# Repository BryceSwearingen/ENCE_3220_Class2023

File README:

This is the readme for embedded systems, more info to be added.

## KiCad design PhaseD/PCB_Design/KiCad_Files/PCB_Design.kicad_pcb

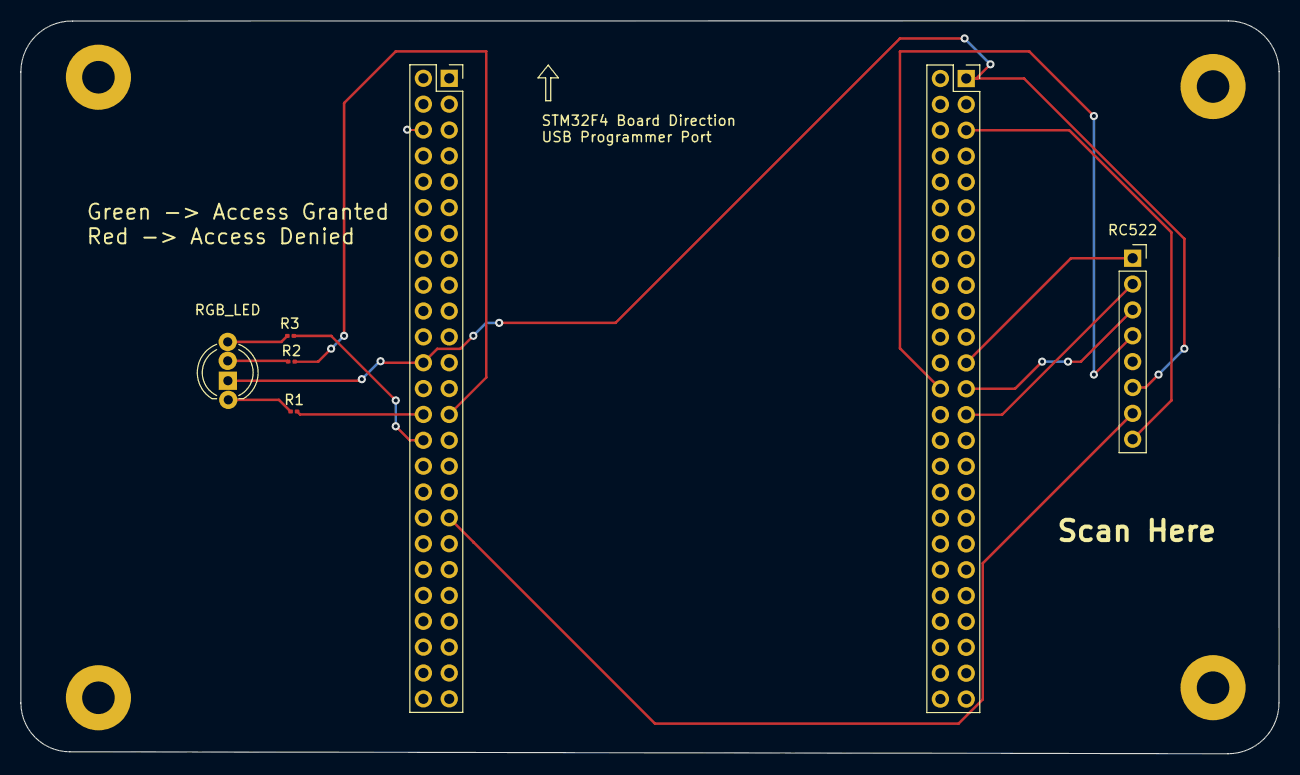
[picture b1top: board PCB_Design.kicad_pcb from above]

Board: 2 copper layers, 123.6 x 72.0 mm, 11 parts (0 on the bottom side), 13 nets.

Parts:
H1, H2, H3, H4: MountingHole; MountingHole_3.2mm_M3_Pad
J1: Discovery Board Conn 1; PinSocket_2x25_P2.54mm_Vertical
J2: Discovery Board Conn 2; PinSocket_2x25_P2.54mm_Vertical
R1, R2, R3: 330; R_0201_0603Metric
RC522: RFID-RC522-MODULE; PinSocket_1x08_P2.54mm_Vertical
RGB_LED: LED_ABGR; LED_D5.0mm-4_RGB_Wide_Pins

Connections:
+3V0: J2.5, RC522.8 (3.3V)
Blue: J1.30, R3.1
GND: J1.24, J2.1, RC522.6 (GND), RGB_LED.1 (A)
Green: J1.27, R2.1
MISO: J2.26, RC522.4 (MISO)
MOSI: J2.25, RC522.3 (MOSI)
unnamed: R3.2, RGB_LED.2 (BK)
unnamed: R2.2, RGB_LED.3 (GK)
unnamed: R1.2, RGB_LED.4 (RK)
RST: J1.35, RC522.7 (RST)
Red: J1.28, R1.1
SCK: J2.27, RC522.2 (SCK)
SDA: J2.23, RC522.1 (SDA)

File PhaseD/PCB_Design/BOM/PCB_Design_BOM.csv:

"Id";"Designator";"Footprint";"Quantity";"Designation";"Supplier and ref";
1;"J2";"PinSocket_2x25_P2.54mm_Vertical";1;"Discovery Board Conn 2";;;
2;"H3,H4,H1,H2";"MountingHole_3.2mm_M3_Pad";4;"MountingHole";;;
3;"R2,R1,R3";"R_0201_0603Metric";3;"330";;;
4;"J1";"PinSocket_2x25_P2.54mm_Vertical";1;"Discovery Board Conn 1";;;
5;"RGB_LED";"LED_D5.0mm-4_RGB_Wide_Pins";1;"LED_ABGR";;;
6;"RC522";"PinSocket_1x08_P2.54mm_Vertical";1;"RFID-RC522-MODULE";;;

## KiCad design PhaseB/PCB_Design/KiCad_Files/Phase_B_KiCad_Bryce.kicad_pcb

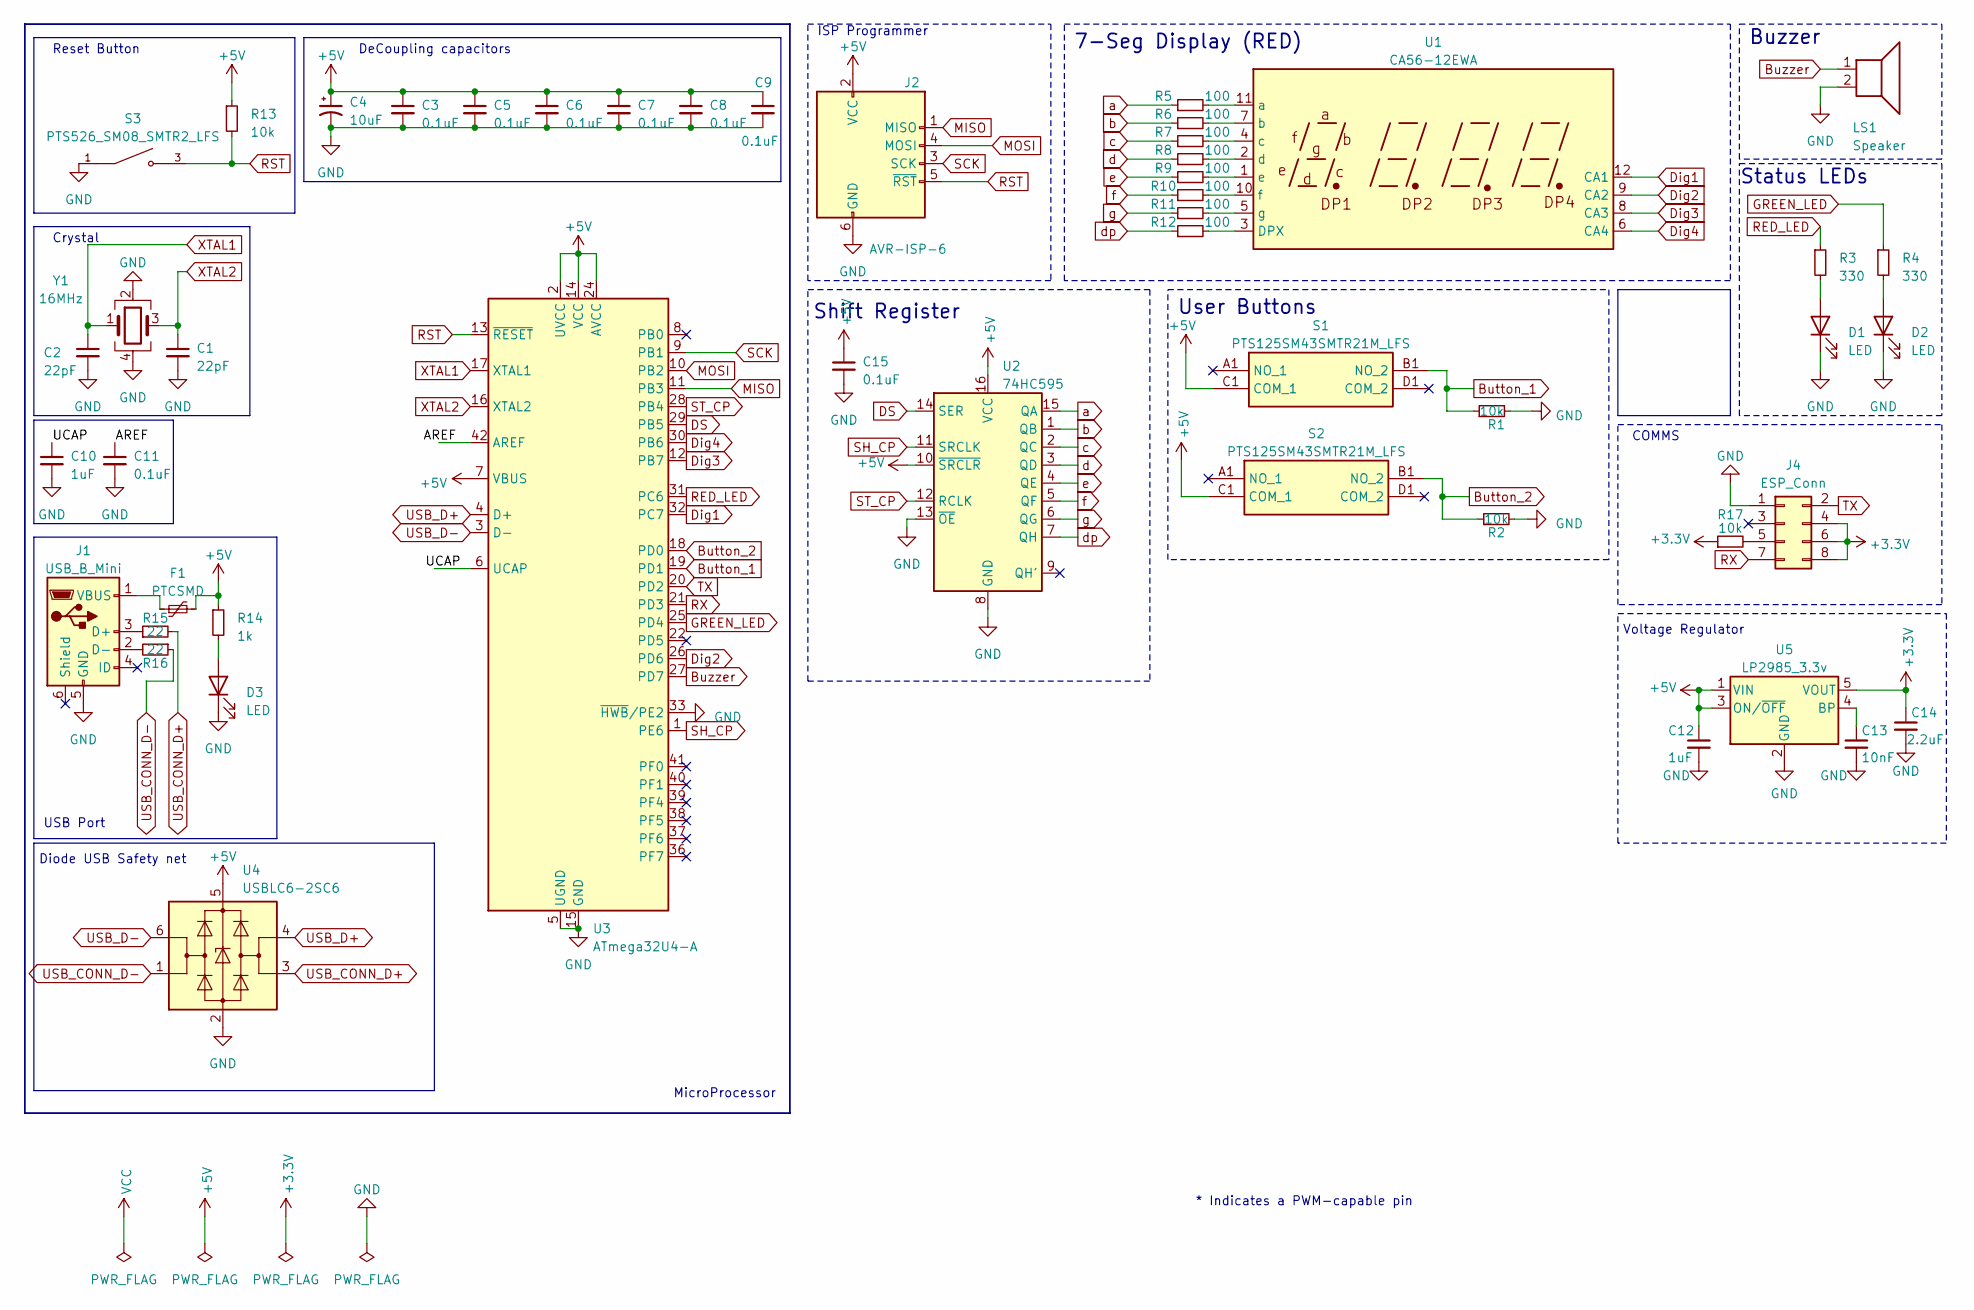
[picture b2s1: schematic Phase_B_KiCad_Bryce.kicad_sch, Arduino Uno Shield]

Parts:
C1, C2: 22pF; C_0603_1608Metric
C3, C5, C6, C7, C8, C9, C11, C15: 0.1uF; C_0603_1608Metric
C4: 10uF; C_0805_2012Metric
C10, C12: 1uF; C_0603_1608Metric
C13: 10nF; C_0603_1608Metric
C14: 2.2uF; C_0603_1608Metric
D1, D2, D3: LED; LED_0805_2012Metric
F1: PTCSMD; Fuse_1812_4532Metric
J1: USB_B_Mini; USB_Mini-B_Lumberg_2486_01_Horizontal
J2: AVR-ISP-6; PinSocket_2x03_P2.54mm_Vertical
J4: ESP_Conn; PinSocket_2x04_P2.54mm_Vertical
LS1: Speaker; Buzzer_12x9.5RM7.6
R1, R2, R13, R17: 10k; R_0603_1608Metric
R3, R4: 330; R_0805_2012Metric
R5, R6, R7, R8, R9, R10, R11, R12: 100; R_0805_2012Metric
R14: 1k; R_0603_1608Metric
R15, R16: 22; R_0603_1608Metric
S1, S2: PTS125SM43SMTR21M_LFS; PTS125_SMD_Button; Manufacturer_Part_Number PTS125SM43SMTR21M LFS; Mouser Part Number 611-PTS125S43SMTRLFS
S3: PTS526_SM08_SMTR2_LFS; PTS526_SMD_Button; PARTREV 20 mar 19
U1: CA56-12EWA
U2: 74HC595; TSSOP-16_4.4x5mm_P0.65mm
U3: ATmega32U4-A; TQFP-44_10x10mm_P0.8mm
U4: USBLC6-2SC6; SOT-23-6
U5: LP2985_3.3v; SOT-23-5
Y1: 16MHz; Crystal_SMD_Abracon_ABM8G-4Pin_3.2x2.5mm

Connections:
+3V3: C14.1, J4.4, J4.6, J4.8, R17.1, U5.5 (VOUT)
+5V: C3.1, C4.1, C5.1, C6.1, C7.1, C8.1, C9.1, C12.1, C15.1, F1.2, J2.2 (VCC), R13.1, R14.1, S1.C1 (COM_1), S2.C1 (COM_1), U2.10 (~SRCLR), U2.16 (VCC), U3.2 (UVCC), U3.7 (VBUS), U3.14 (VCC), U3.24 (AVCC), U3.34 (VCC), U3.44 (AVCC), U4.5 (VBUS), U5.1 (VIN), U5.3 (ON/~OFF)
/AREF: C11.1, U3.42 (AREF)
/UCAP: C10.1, U3.6 (UCAP)
Button_1: R1.1, S1.B1 (NO_2), U3.19 (PD1)
Button_2: R2.1, S2.B1 (NO_2), U3.18 (PD0)
Buzzer: LS1.1, U3.27 (PD7)
DS: U2.14 (SER), U3.29 (PB5)
Dig1: U1.12 (CA1), U3.32 (PC7)
Dig2: U1.9 (CA2), U3.26 (PD6)
Dig3: U1.8 (CA3), U3.12 (PB7)
Dig4: U1.6 (CA4), U3.30 (PB6)
GND: C1.2, C2.2, C3.2, C4.2, C5.2, C6.2, C7.2, C8.2, C9.2, C10.2, C11.2, C12.2, C13.2, C14.2, C15.2, D1.1 (K), D2.1 (K), D3.1 (K), J1.5 (GND), J2.6 (GND), J4.1, LS1.2, R1.2, R2.2, S3.1, U2.8 (GND), U2.13 (~OE), U3.5 (UGND), U3.15 (GND), U3.23 (GND), U3.33 (~HWB/PE2), U3.35 (GND), U3.43 (GND), U4.2 (GND), U5.2 (GND), Y1.2, Y1.4
GREEN_LED: R4.1, U3.25 (PD4)
MISO: J2.1 (MISO), U3.11 (PB3)
MOSI: J2.4 (MOSI), U3.10 (PB2)
unnamed: D1.2 (A), R3.2
unnamed: D2.2 (A), R4.2
unnamed: D3.2 (A), R14.2
unnamed: J1.3 (D+), R15.1
unnamed: J1.2 (D-), R16.2
unnamed: F1.1, J1.1 (VBUS)
unnamed: J4.5, R17.2
unnamed: R12.2, U1.3 (DPX)
unnamed: R5.2, U1.11 (a)
unnamed: R6.2, U1.7 (b)
unnamed: R7.2, U1.4 (c)
unnamed: R8.2, U1.2 (d)
unnamed: R9.2, U1.1 (e)
unnamed: R10.2, U1.10 (f)
unnamed: R11.2, U1.5 (g)
unnamed: C13.1, U5.4 (BP)
RED_LED: R3.1, U3.31 (PC6)
RST: J2.5 (~RST), R13.2, S3.3, U3.13 (~RESET)
RX: J4.7, U3.21 (PD3)
SCK: J2.3 (SCK), U3.9 (PB1)
SH_CP: U2.11 (SRCLK), U3.1 (PE6)
ST_CP: U2.12 (RCLK), U3.28 (PB4)
TX: J4.2, U3.20 (PD2)
USB_CONN_D+: R15.2, U4.3 (I/O2)
USB_CONN_D-: R16.1, U4.1 (I/O1)
USB_D+: U3.4 (D+), U4.4 (I/O2)
USB_D-: U3.3 (D-), U4.6 (I/O1)
XTAL1: C2.1, U3.17 (XTAL1), Y1.1
XTAL2: C1.1, U3.16 (XTAL2), Y1.3
a: R5.1, U2.15 (QA)
b: R6.1, U2.1 (QB)
c: R7.1, U2.2 (QC)
d: R8.1, U2.3 (QD)
dp: R12.1, U2.7 (QH)
e: R9.1, U2.4 (QE)
f: R10.1, U2.5 (QF)
g: R11.1, U2.6 (QG)

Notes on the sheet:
Shift Register
USB Port
Voltage Regulator
Status LEDs
MicroProcessor
DeCoupling capacitors
User Buttons
Buzzer
ISP Programmer
Reset Button
* Indicates a PWM-capable pin
COMMS
Crystal
7-Seg Display (RED)
Diode USB Safety net

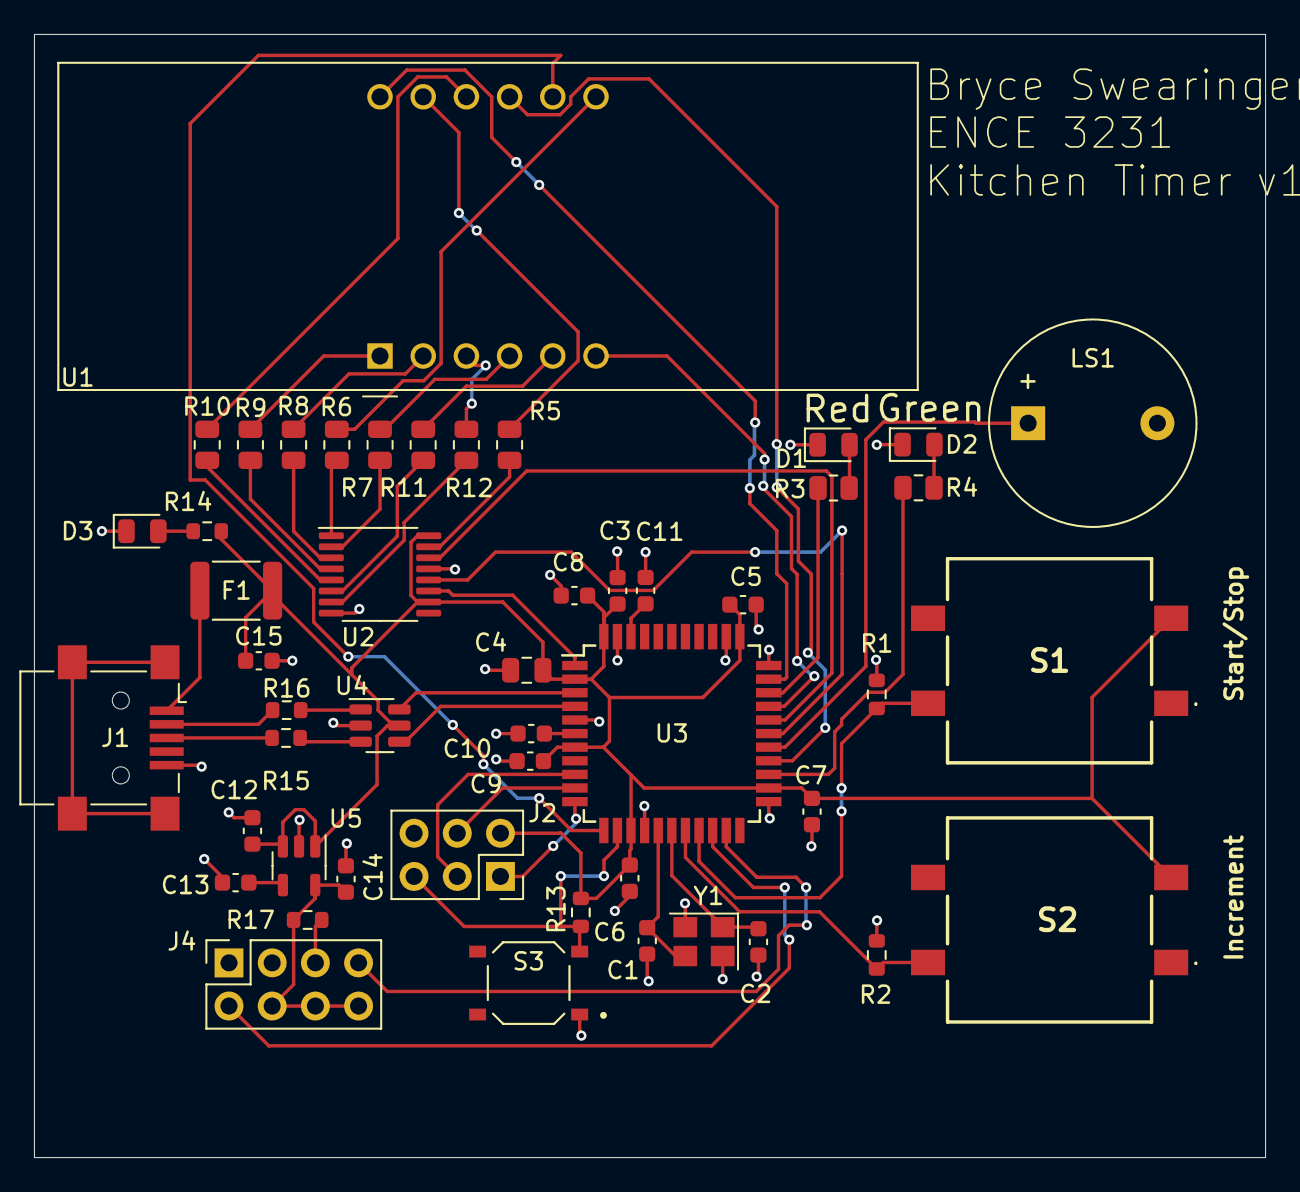
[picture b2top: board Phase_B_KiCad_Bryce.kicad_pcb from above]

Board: 2 copper layers, 72.4 x 66.0 mm, 49 parts (0 on the bottom side), 53 nets.

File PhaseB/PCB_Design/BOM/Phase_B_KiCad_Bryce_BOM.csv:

"Id";"Designator";"Footprint";"Quantity";"Designation";"Supplier and ref";
1;"R12,R9,R5,R7,R10,R8,R6,R11";"R_0805_2012Metric";8;"100";;;
2;"S3";"PTS526_SMD_Button";1;"PTS526_SM08_SMTR2_LFS";;;
3;"R14";"R_0603_1608Metric";1;"1k";;;
4;"U2";"TSSOP-16_4.4x5mm_P0.65mm";1;"74HC595";;;
5;"LS1";"Buzzer_12x9.5RM7.6";1;"Speaker";;;
6;"C12,C10";"C_0603_1608Metric";2;"1uF";;;
7;"C8,C3,C15,C9,C11,C5,C7,C6";"C_0603_1608Metric";8;"0.1uF";;;
8;"J4";"PinSocket_2x04_P2.54mm_Vertical";1;"ESP_Conn";;;
9;"F1";"Fuse_1812_4532Metric";1;"PTCSMD";;;
10;"D3,D1,D2";"LED_0805_2012Metric";3;"LED";;;
11;"U4";"SOT-23-6";1;"USBLC6-2SC6";;;
12;"R17,R1,R2,R13";"R_0603_1608Metric";4;"10k";;;
13;"Y1";"Crystal_SMD_Abracon_ABM8G-4Pin_3.2x2.5mm";1;"16MHz";;;
14;"C4";"C_0805_2012Metric";1;"10uF";;;
15;"J2";"PinSocket_2x03_P2.54mm_Vertical";1;"AVR-ISP-6";;;
16;"C14";"C_0603_1608Metric";1;"2.2uF";;;
17;"R3,R4";"R_0805_2012Metric";2;"330";;;
18;"R16,R15";"R_0603_1608Metric";2;"22";;;
19;"J1";"USB_Mini-B_Lumberg_2486_01_Horizontal";1;"USB_B_Mini";;;
20;"U5";"SOT-23-5";1;"LP2985_3.3v";;;
21;"S2,S1";"PTS125_SMD_Button";2;"PTS125SM43SMTR21M_LFS";;;
22;"C13";"C_0603_1608Metric";1;"10nF";;;
23;"U3";"TQFP-44_10x10mm_P0.8mm";1;"ATmega32U4-A";;;
24;"C2,C1";"C_0603_1608Metric";2;"22pF";;;
25;"U1";"CA56-12EWA";1;"CA56-12EWA";;;

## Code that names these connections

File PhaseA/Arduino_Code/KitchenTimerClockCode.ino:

#define BUTTON_1  2
#define BUTTON_2  3
#define GREEN_LED 4
#define RED_LED   5
//#define BUZZER    6

#define DATA      9
#define LATCH     8
#define CLOCK     7

#define DIGIT_4   10
#define DIGIT_3   11
#define DIGIT_2   12
#define DIGIT_1   13
 
unsigned char table[]=
{ 0b00111111, // 0
  0b00000110, // 1
  0b01011011, // 2
  0b01001111, // 3
  0b01100110, // 4
  0b01101101, // 5
  0b01111101, // 6
  0b00000111, // 7
  0b01111111, // 8
  0b01101111  // 9
  };

unsigned char count = 30;
unsigned char initialValue = 30;
unsigned int buttonState = 0;  // variable for reading the pushbutton status
int countdown = 10;

volatile unsigned char isr_1_flag = 0;
volatile unsigned char isr_2_flag = 0;
volatile unsigned char isr_3_flag = 0;

void setup() {
 // LEDs Pins
  pinMode(RED_LED, OUTPUT);
  pinMode(GREEN_LED, OUTPUT);

  // Button Pins
  pinMode(BUTTON_1, INPUT_PULLUP);
  attachInterrupt(digitalPinToInterrupt(BUTTON_1), Button_1_ISR, CHANGE);
  pinMode(BUTTON_2, INPUT_PULLUP);
  attachInterrupt(digitalPinToInterrupt(BUTTON_2), Button_2_ISR, CHANGE);

  // 7-Seg Display
  pinMode(DIGIT_1, OUTPUT);
  pinMode(DIGIT_2, OUTPUT);
  pinMode(DIGIT_3, OUTPUT);
  pinMode(DIGIT_4, OUTPUT);

  // Shift Register Pins
  pinMode(LATCH, OUTPUT);
  pinMode(CLOCK, OUTPUT);
  pinMode(DATA, OUTPUT);

  //disp_on();

  // initialize timer1 
  noInterrupts();           // disable all interrupts
  TCCR1A = 0;
  TCCR1B = 0;
  TCNT1  = 0;
  OCR1A = 62500 / 1000;            // compare match register 16MHz/256
  TCCR1B |= (1 << WGM12);   // CTC mode
  TCCR1B |= (1 << CS12);    // 256 prescaler 
  TIMSK1 |= (1 << OCIE1A);  // enable timer compare interrupt
  interrupts();             // enable all interrupts
}

void Display_Numbers()
{
  disp_on1();
  digitalWrite(LATCH, LOW);
  shiftOut(DATA, CLOCK, MSBFIRST, table[0]);
  digitalWrite(LATCH, HIGH);
  delay(250);
  disp_on2();
  digitalWrite(LATCH, LOW);
  shiftOut(DATA, CLOCK, MSBFIRST, table[0]);
  digitalWrite(LATCH, HIGH);
  delay(250);
  disp_on3();
  digitalWrite(LATCH, LOW);
  shiftOut(DATA, CLOCK, MSBFIRST, table[countdown / 10]);
  digitalWrite(LATCH, HIGH);
  delay(250);
  disp_on4();
  digitalWrite(LATCH, LOW);
  shiftOut(DATA, CLOCK, MSBFIRST, table[countdown % 10]);
  digitalWrite(LATCH, HIGH);
  delay(250);
  countdown = countdown-0.000001;
  
}

// void Display_Numbers()
// {
//   Display(count);
// if(countdown == 0)
//    {
//      countdown = initialValue;
//    }
//   // Reset Counter

// }

void disp_on1()
{
   digitalWrite(DIGIT_1, LOW);
   digitalWrite(DIGIT_2, HIGH);
   digitalWrite(DIGIT_3, HIGH);
   digitalWrite(DIGIT_4, HIGH);
}
void disp_on2()
{
   digitalWrite(DIGIT_1, HIGH);
   digitalWrite(DIGIT_2, LOW);
   digitalWrite(DIGIT_3, HIGH);
   digitalWrite(DIGIT_4, HIGH);
}
void disp_on3()
{
   digitalWrite(DIGIT_1, HIGH);
   digitalWrite(DIGIT_2, HIGH);
   digitalWrite(DIGIT_3, LOW);
   digitalWrite(DIGIT_4, HIGH);
}
void disp_on4()
{
   digitalWrite(DIGIT_1, HIGH);
   digitalWrite(DIGIT_2, HIGH);
   digitalWrite(DIGIT_3, HIGH);
   digitalWrite(DIGIT_4, LOW);
}

void Button_1_ISR()
{
  unsigned int buttonState = 0;  // variable for reading the pushbutton status
    
  buttonState = digitalRead(BUTTON_1);
  digitalWrite(RED_LED, buttonState);

  count++;
  Display_Numbers();
}

void Button_2_ISR()
{ 
  unsigned int buttonState = 0;  // variable for reading the pushbutton status
   
  buttonState = digitalRead(BUTTON_2);
  digitalWrite(GREEN_LED, buttonState);
}

ISR(TIMER1_COMPA_vect) // timer compare interrupt service routine
{
  // Set ISR Flag
  isr_3_flag = 1;
}

void loop() {
   Display_Numbers();
  // Attend Button 1
  if(isr_1_flag == 1)
  {
    // Reset ISR Flag
    isr_1_flag = 0;

    // Code
    count++;
    if (count > initialValue){
      count = 0;
    }
    buttonState = digitalRead(BUTTON_1);
    digitalWrite(RED_LED, buttonState);
  }

  // Attend Button 2
  if(isr_2_flag == 1)
  {
    // Reset ISR Flag
    isr_2_flag = 0;
    
    // Code
    buttonState = digitalRead(BUTTON_2);
    digitalWrite(GREEN_LED, buttonState);
  }

  // Attend 7-Seg Display
  if(isr_3_flag == 1)
  {
    // Reset ISR Flag
    isr_3_flag = 0;

    // Code
    //count--;
  }
}

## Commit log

2023-04-07 Create PhaseA_Final_Code
    Kitchen Timer code with countdown and buzzer features, button interupts.
2023-04-07 Create Block Diagrams
    All block diagrams.
2023-04-07 Create KiCadFiles
2023-04-07 Made Some Changes
2023-04-07 Phase A Beta Release
2023-04-12 Add files via upload
    Schematic and PCB layout created in KiCad
2023-04-12 PhaseA_Beta
2023-04-12 Phase_A_Beta
2023-04-20 Phase_B_PCB_Design
2023-04-20 Phase_B_Release
2023-04-20 Naming Conventions
2023-04-21 Final Updates
2023-04-21 The Final Push
2023-04-29 April 28 Changes
2023-05-04 Beta Release
2023-05-25 Code
2023-05-29 Beta
2023-06-01 Removed ReadMe
2023-06-08 Beta_Release_Final
